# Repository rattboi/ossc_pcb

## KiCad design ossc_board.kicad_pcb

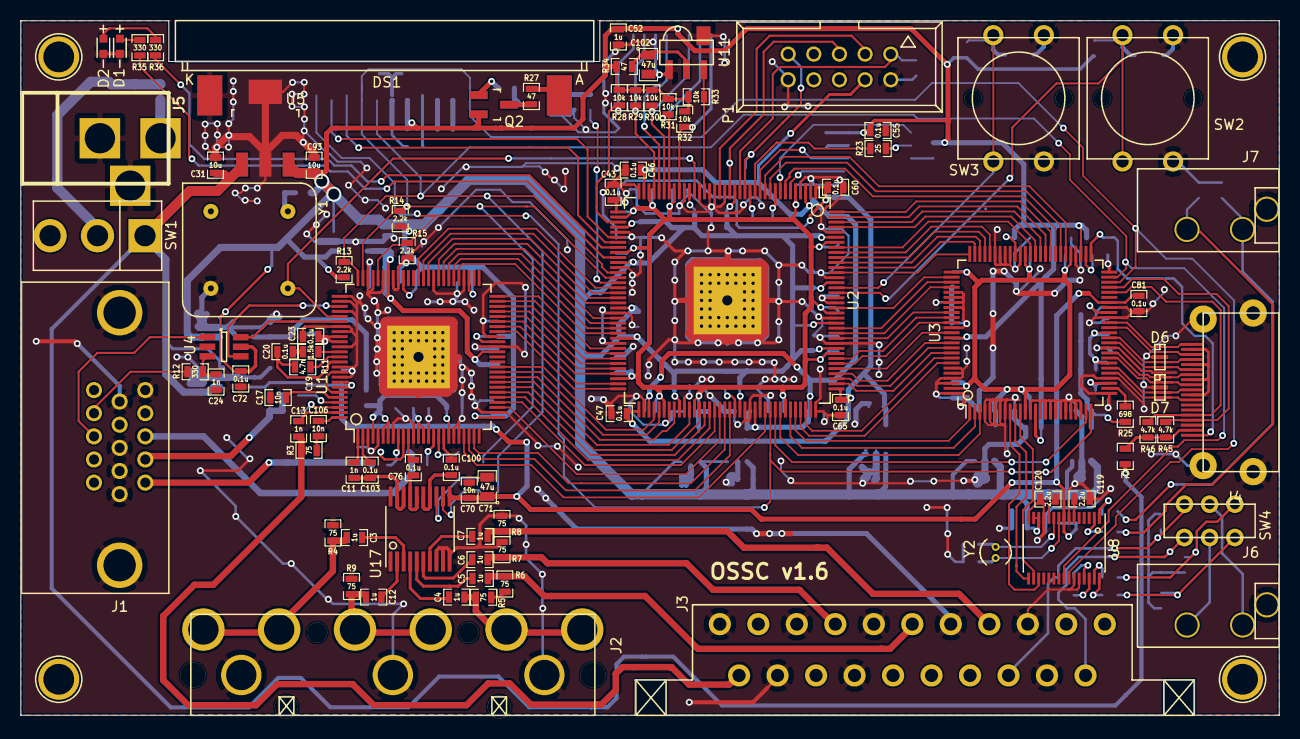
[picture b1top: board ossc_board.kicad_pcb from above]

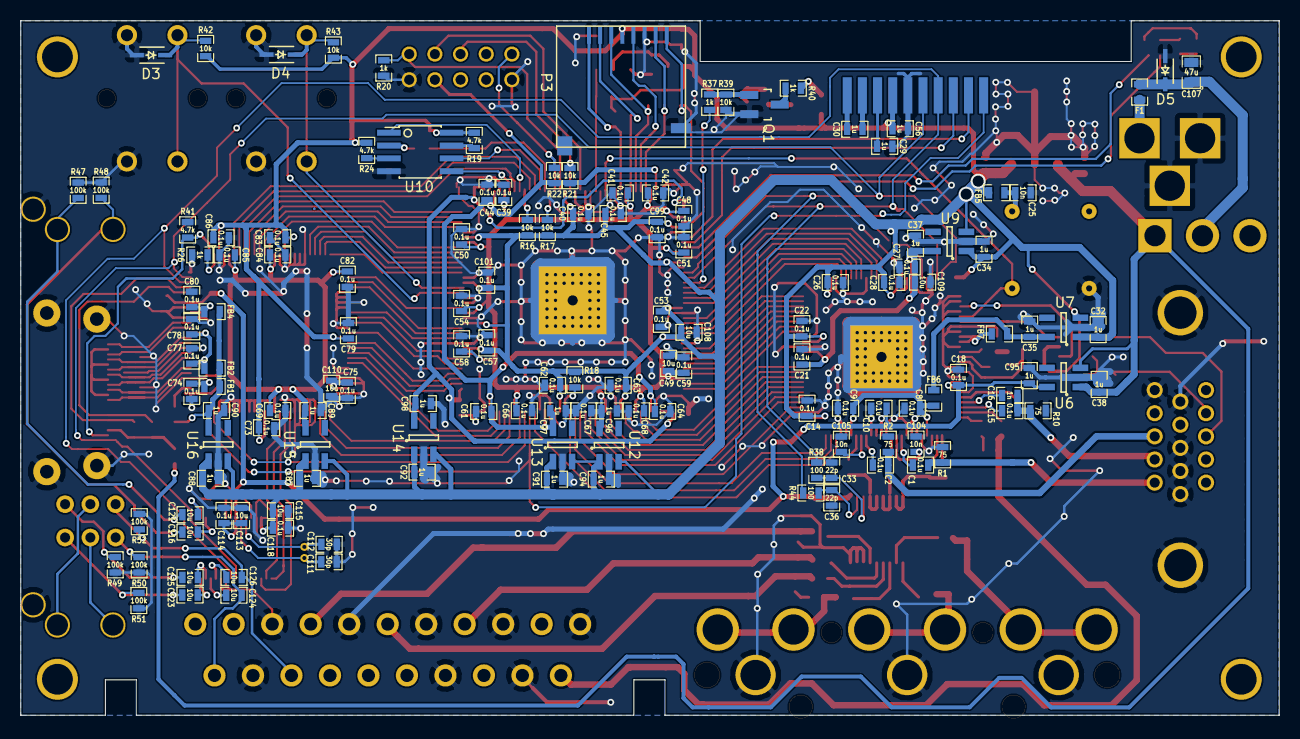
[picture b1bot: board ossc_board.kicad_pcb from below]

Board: 2 copper layers, 124.6 x 68.7 mm, 230 parts (138 on the bottom side), 197 nets.

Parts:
C1, C2, C8, C9, C10, C14, C15, C18, C20, C21, C22, C23, C26, C27, C28, C39, C40, C41, C42, C43, C44, C45, C46, C47, C48, C50, C51, C53, C54, C55, C57, C58, C59, C60, C61, C62, C63, C64, C65, C66, C67, C68, C69, C72, C73, C74, C75, C76, C77, C78, C79, C80, C81, C82, C83, C84, C85, C86, C99, C100, C101, C103, C114, C118: 0.1u; SM0603_Capa_libcms
C3, C4, C5, C6, C7, C12, C29, C30, C32, C34, C35, C37, C38, C52, C56, C87, C88, C89, C90, C91, C92, C94, C95, C96, C97, C98: 1u; SM0603_Capa_libcms
C11, C13, C16, C24: 1n; SM0603_Capa_libcms
C17, C25, C70, C104, C105, C106: 10n; SM0603_Capa_libcms
C19: 4.7n; SM0603_Capa_libcms
C31, C49, C93, C108, C109, C110, C113, C115, C116, C121, C123, C124, C125, C126: 10u; SM0603_Capa_libcms
C33, C36: 22p; SM0603_Capa_libcms
C71, C102, C107: 47u; SM0805_libcms
C111, C112: 30p; SM0603_Capa_libcms
C119, C120: 2.2u; SM0603_Capa_libcms
D1: LEDR; LED-0603
D2: LEDG; LED-0603
D3, D4, D5: SD05-7; SOD-323_Handsoldering
D6, D7: RClamp0524P; SLP2510P8
DS1: CONN_01X12; NHD-C0216CZ_vertmount
F1: F0603E1R50FSTR; SM0603_Resistor_libcms
F2: MF-FSMF020X-2; SM0603_Resistor_libcms
FB1, FB2, FB4, FB5, FB6, FB7: MPZ1608S221A; SM0603_Resistor_libcms
J1: VGA; VGA_CONN
J2: 3XRCA_CONN; 3xRCA_CONN
J3: SCART-F; SCART_CONN
J4: HDMI_CONN; HDMI_CONN-10029449-111RLF
J5: 5VDC_IN; BARREL_JACK_roundconn
J6, J7: SJ1-3533NG
MH1, MH2, MH3, MH4: CONN_1; 1pin
P1: JTAG_CONN; VASCH5x2
P3: mSD_CONN; DM3D-SF
Q1: BC847; SOT-23_Handsoldering
Q2: BC857; SOT-23_Handsoldering
R1, R2, R3, R4, R5, R6, R7, R8, R9, R10: 75; SM0603_Resistor_libcms
R11: 1.5k; SM0603_Resistor_libcms
R12, R35, R36: 330; SM0603_Resistor_libcms
R13, R14, R15: 2.2k; SM0603_Resistor_libcms
R16, R17, R18, R21, R22, R28, R29, R30, R31, R32, R33, R39, R42, R43: 10k; SM0603_Resistor_libcms
R19, R24, R41, R45, R46: 4.7k; SM0603_Resistor_libcms
R20, R26, R37, R40: 1k; SM0603_Resistor_libcms
R23: 25; SM0603_Resistor_libcms
R25: 698; SM0603_Resistor_libcms
R27, R34: 47; SM0603_Resistor_libcms
R38, R44: 100; SM0603_Resistor_libcms
R47, R48, R49, R50, R51, R52: 100k; SM0603_Resistor_libcms
SW1: SPST; SW_SPDT
SW2, SW3: SW_PUSH; SW_PUSH-SKHCBFA010
SW4: DPDT; MS22
U1: TVP7002PZP; TQFP-100_thermal
U2: EP4CE15E22; TQFP-144_thermal
U3: IT6613; TQFP-100_custom
U4: SN74LVC2G17; SOT-23-6_Handsoldering
U5: AP7361C; SOT-223_Handsoldering
U6: TLV70033; SOT-23-5_Handsoldering
U7: NCP703SN19T1G; SOT-23-5_Handsoldering
U8: PCM1862; TSSOP-30_4.4x7.8mm_Pitch0.5mm_Handsoldering
U9: TLV70019; SOT-23-5_Handsoldering
U10: S25FL216K; SOIC-8_3.9x4.9mm_Pitch1.27mm_Handsoldering
U11: IRM-V538/TR1; IRM-V5XX_TR1
U12, U14: TLV70012; SOT-23-5_Handsoldering
U13: TLV70025; SOT-23-5_Handsoldering
U15, U16: TLV70018; SOT-23-5_Handsoldering
U17: THS7353; TSSOP-20_4.4x6.5mm_Pitch0.65mm_Handsoldering
Y1: ACHL-27MHZ-EK; ACHL-OSC
Y2: 24.576MHz; ECS-3X9X

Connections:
/fpga1/ASDO: U2.6, U10.5
/fpga1/BTN0: D3.1, R42.1, SW2.1, U2.128
/fpga1/BTN1: D4.1, R43.1, SW3.1, U2.129
/fpga1/CLK27: U1.80, U2.25, Y1.5
/fpga1/DATA0: R23.1, U2.13
/fpga1/DCLK: U2.12, U10.6
/fpga1/HDMITX_HSYNC: U2.103, U3.2
/fpga1/HDMITX_INT_N: U2.100, U3.24
/fpga1/HDMITX_PCLK: U2.113, U3.88
/fpga1/HDMITX_R0: U2.137, U3.63
/fpga1/HDMITX_R1: U2.141, U3.62
/fpga1/HDMITX_R2: U2.142, U3.61
/fpga1/HDMITX_R3: U2.143, U3.60
/fpga1/HDMITX_R4: U2.144, U3.59
/fpga1/HDMITX_R5: U2.7, U3.58
/fpga1/HDMITX_R6: U2.10, U3.57
/fpga1/HDMITX_R7: U2.11, U3.56
/fpga1/HDMITX_VSYNC: U2.101, U3.3
/fpga1/IR_RX: R33.2, U2.23, U11.1
/fpga1/LCD_BLEN: R37.2, U2.51
/fpga1/LCD_CS_N: DS1.3, U2.43
/fpga1/LCD_RS: DS1.2, U2.42
/fpga1/LED0: R35.2, U2.46
/fpga1/LED1: R36.2, U2.44
/fpga1/RESET_N: DS1.1, R15.1, U1.71, U2.99, U3.25
/fpga1/SCL: DS1.4, R14.2, R38.2, U1.74, U2.50, U3.48, U8.24
/fpga1/SDA: DS1.5, R13.1, R44.1, U1.75, U2.49, U3.49, U8.23
/fpga1/SD_CLK: P3.5, U2.32
/fpga1/SD_CMD: P3.3, R30.1, U2.31
/fpga1/SD_DAT0: P3.7, R29.1, U2.33
/fpga1/SD_DAT1: P3.8, R28.1, U2.39
/fpga1/SD_DAT2: P3.1, R32.1, U2.28
/fpga1/SD_DAT3: P3.2, R31.1, U2.30
/fpga1/TCK: P1.1, R20.2, U2.16
/fpga1/TDI: P1.9, R22.2, U2.15
/fpga1/TDO: P1.3, U2.20
/fpga1/TMS: P1.5, R21.2, U2.18
/fpga1/VCCA: C44.1, C46.1, C61.1, C64.1, C97.1, P1.4, R21.1, R22.1, U2.3, U2.35, U2.75, U2.96, U2.107, U13.5
/fpga1/VCCD_PLL: C43.1, C47.1, C60.1, C65.1, C98.1, U2.1, U2.37, U2.73, U2.109, U14.5
/fpga1/VCCINT: C39.1, C41.1, C42.1, C48.1, C49.1, C50.1, C51.1, C54.1, C58.1, C59.1, C66.1, C67.1, C68.1, C96.1, U2.5, U2.29, U2.34, U2.38, U2.45, U2.70, U2.78, U2.84, U2.102, U2.116, U2.124, U2.138, U12.5
/fpga1/nCSO: U2.8, U10.1
/hdmitx1/5V: C31.1, C38.1, F2.1, SW1.1, U5.1, U6.1, U6.3
/hdmitx1/5V_FUSED: F2.2, J4.18, R45.1, R46.1
/hdmitx1/AV1_AUD_L: C126.2, J3.6, R52.1, SW4.3
/hdmitx1/AV1_AUD_R: C124.2, J3.2, R50.2, SW4.6
/hdmitx1/AV2_AUD_L: C125.2, R49.1, SW4.1
/hdmitx1/AV2_AUD_R: C123.2, R51.2, SW4.4
/hdmitx1/AV3_AUD_L: C121.1, J7.2, R47.2
/hdmitx1/AV3_AUD_R: C116.1, J7.3, R48.2
/hdmitx1/AVCC1V8: C90.1, FB1.1, FB2.1, FB4.1, R25.2, U16.5
/hdmitx1/AVDD3V3: C10.1, C18.2, C70.1, C71.1, C81.1, C95.1, C113.1, C114.1, U1.13, U1.14, U1.93, U1.94, U3.44, U6.5, U8.8, U17.11
/hdmitx1/B0: U2.105, U3.94
/hdmitx1/B1: U2.106, U3.93
/hdmitx1/B2: U2.110, U3.92
/hdmitx1/B3: U2.111, U3.91
/hdmitx1/B4: U2.112, U3.90
/hdmitx1/B5: U2.114, U3.86
/hdmitx1/B6: U2.115, U3.85
/hdmitx1/B7: U2.119, U3.84
/hdmitx1/DDC_SCL: J4.15, R46.2, U3.46
/hdmitx1/DDC_SDA: J4.16, R45.2, U3.47
/hdmitx1/DE: U2.104, U3.1
/hdmitx1/DVDD1V8: C69.1, C75.1, C82.1, C84.1, C85.1, C89.1, C110.1, U3.12, U3.55, U3.64, U3.76, U3.99, U15.5
/hdmitx1/DVDD3V3: C14.1, C22.1, C26.1, C28.1, C32.2, C34.1, C40.1, C45.1, C52.1, C53.1, C55.2, C56.2, C57.1, C62.1, C63.1, C72.1, C73.1, C79.1, C83.1, C86.1, C87.1, C88.1, C91.1, C92.1, C93.1, C94.1, C99.1, C101.1, C108.1, C115.1, C118.1, DS1.7, FB5.2, P3.4, Q2.2, R13.2, R14.1, R16.1, R17.2, R18.1, R19.2, R24.2, R28.2, R29.2, R30.2, R31.2, R32.2, R33.1, R34.2, R42.2, R43.2, U1.26, U1.41, U1.53, U1.66, U2.17, U2.26, U2.40, U2.47, U2.56, U2.62, U2.81, U2.93, U2.117, U2.122, U2.130, U2.139, U3.14, U3.53, U3.66, U3.89, U4.5, U5.3, U7.1, U7.3, U8.13, U8.14, U9.1, U9.3, U10.8, U12.1, U12.3, U13.1, U13.3, U14.1, U14.3, U15.1, U15.3, U16.1, U16.3
/hdmitx1/G0: U2.120, U3.79
/hdmitx1/G1: U2.121, U3.78
/hdmitx1/G2: U2.125, U3.77
/hdmitx1/G3: U2.132, U3.75
/hdmitx1/G4: U2.133, U3.74
/hdmitx1/G5: U2.134, U3.73
/hdmitx1/G6: U2.135, U3.72
/hdmitx1/G7: U2.136, U3.71
/hdmitx1/HPD: J4.19, R41.1, U3.51
/hdmitx1/I2S_BCK: U3.11, U8.17
/hdmitx1/I2S_DATA: U3.9, U8.18
/hdmitx1/I2S_WS: U3.10, U8.16
/hdmitx1/TMDS_CLK+: D7.4, D7.7, J4.10, U3.31
/hdmitx1/TMDS_CLK-: D7.5, D7.6, J4.12, U3.30
/hdmitx1/TMDS_D0+: D7.1, D7.10, J4.7, U3.34
/hdmitx1/TMDS_D0-: D7.2, D7.9, J4.9, U3.33
/hdmitx1/TMDS_D1+: D6.4, D6.7, J4.4, U3.37
/hdmitx1/TMDS_D1-: D6.5, D6.6, J4.6, U3.36
/hdmitx1/TMDS_D2+: D6.1, D6.10, J4.1, U3.40
/hdmitx1/TMDS_D2-: D6.2, D6.9, J4.3, U3.39
/tvp_board1/AVDD: C35.1, FB6.1, FB7.1, U7.5
/tvp_board1/AVDD_F: C8.1, C9.1, FB6.2, U1.4, U1.6, U1.7, U1.19
/tvp_board1/B0: U1.36, U2.76
/tvp_board1/B1: U1.35, U2.77
/tvp_board1/B2: U1.34, U2.80
/tvp_board1/B3: U1.33, U2.83
/tvp_board1/B4: U1.32, U2.85
/tvp_board1/B5: U1.31, U2.86
/tvp_board1/B6: U1.30, U2.87
/tvp_board1/B7: U1.29, U2.88
/tvp_board1/DVDD: C21.1, C27.1, C37.1, C109.1, U1.39, U1.69, U9.5
/tvp_board1/FID: U1.22, U2.98
/tvp_board1/G0: U1.50, U2.64
/tvp_board1/G1: U1.49, U2.65
/tvp_board1/G2: U1.48, U2.66
/tvp_board1/G3: U1.47, U2.67
/tvp_board1/G4: U1.46, U2.68
/tvp_board1/G5: U1.45, U2.69
/tvp_board1/G6: U1.44, U2.71
/tvp_board1/G7: U1.43, U2.72
/tvp_board1/HSYNC: U1.24, U2.90
/tvp_board1/PCLK: U1.28, U2.89
/tvp_board1/R0: U1.63, U2.52
/tvp_board1/R1: U1.62, U2.53
/tvp_board1/R2: U1.61, U2.54
/tvp_board1/R3: U1.59, U2.55
/tvp_board1/R4: U1.58, U2.58
/tvp_board1/R5: U1.57, U2.59
/tvp_board1/R6: U1.56, U2.60
/tvp_board1/R7: U1.55, U2.61
/tvp_board1/RGB1_B: C7.1, J3.7, R8.1
/tvp_board1/RGB1_G: C5.1, J3.11, R6.1
/tvp_board1/RGB1_R: C6.1, J3.15, R7.1
/tvp_board1/RGB1_S: C13.1, J3.20, R3.1
/tvp_board1/RGB2_B: C4.1, J2.2, R5.1
/tvp_board1/RGB2_G: C12.1, J2.1, R9.1
/tvp_board1/RGB2_R: C3.1, J2.3, R4.1
/tvp_board1/RGB3_B: C2.1, J1.3, R2.1
/tvp_board1/RGB3_G: C15.1, C16.1, J1.2, R10.2
/tvp_board1/RGB3_HS: J1.13, U4.1
/tvp_board1/RGB3_HS_B: U1.81, U4.6
/tvp_board1/RGB3_R: C1.1, J1.1, R1.1
/tvp_board1/RGB3_VS: J1.14, R12.2
/tvp_board1/RGB3_VS_B: U1.78, U4.4
/tvp_board1/RGB_12_B: C100.1, U17.14, U17.15
/tvp_board1/RGB_12_G: C11.1, C103.1, U17.18, U17.19
/tvp_board1/RGB_12_R: C76.1, U17.16, U17.17
/tvp_board1/VSYNC: U1.23, U2.91
GND: C8.2, C9.2, C10.2, C14.2, C17.1, C18.1, C21.2, C22.2, C23.2, C24.2, C25.2, C26.2, C27.2, C28.2, C29.1, C31.2, C32.1, C33.1, C34.2, C35.2, C36.2, C37.2, C38.2, C39.2, C40.2, C41.2, C42.2, C43.2, C44.2, C45.2, C46.2, C47.2, C48.2, C49.2, C50.2, C51.2, C52.2, C53.2, C54.2, C55.1, C56.1, C57.2, C58.2, C59.2, C60.2, C61.2, C62.2, C63.2, C64.2, C65.2, C66.2, C67.2, C68.2, C69.2, C70.2, C71.2, C72.2, C73.2, C74.2, C75.2, C77.2, C78.2, C79.2, C80.2, C81.2, C82.2, C83.2, C84.2, C85.2, C86.2, C87.2, C88.2, C89.2, C90.2, C91.2, C92.2, C93.2, C94.2, C95.2, C96.2, C97.2, C98.2, C99.2, C101.2, C102.2, C104.1, C105.1, C106.2, C107.2, C108.2, C109.2, C110.2, C111.2, C112.2, C113.2, C114.2, C115.2, C118.2, C119.2, C120.2, D1.2, D2.2, D3.2, D4.2, D5.2, D6.3, D6.8, D7.3, D7.8, DS1.6, DS1.12, J1.5, J1.6, J1.7, J1.8, J1.10, J2.4, J3.4, J3.5, J3.9, J3.13, J3.14, J3.17, J3.18, J3.21, J4.2, J4.5, J4.8, J4.11, J4.17, J5.2, J5.3, J6.1, J7.1, P1.2, P1.10, P3.6, Q1.2, R1.2, R2.2, R3.2, R4.2, R5.2, R6.2, R7.2, R8.2, R9.2, R10.1, R15.2, R20.1, R26.2, R39.2, R41.2, R47.1, R48.1, R49.2, R50.1, R51.1, R52.2, SW2.2, SW3.2, U1.3, U1.5, U1.8, U1.12, U1.15, U1.20, U1.21, U1.27, U1.40, U1.42, U1.54, U1.60, U1.67, U1.68, U1.70, U1.72, U1.73, U1.76, U1.77, U1.79, U1.82, U1.83, U1.86, U1.90, U1.91, U1.92, U1.95, U2.2, U2.4, U2.19, U2.21, U2.22, U2.24, U2.27, U2.36, U2.41, U2.48, U2.57, U2.63, U2.74, U2.79, U2.82, U2.94, U2.95, U2.97, U2.108, U2.118, U2.123, U2.126, U2.127, U2.131, U2.140, U3.4, U3.5, U3.6, U3.7, U3.8, U3.13, U3.15, U3.16, U3.17, U3.18, U3.19, U3.20, U3.21, U3.22, U3.23, U3.26, U3.29, U3.35, U3.41, U3.43, U3.50, U3.54, U3.65, U3.67, U3.68, U3.69, U3.70, U3.80, U3.81, U3.82, U3.83, U3.87, U3.95, U3.96, U3.97, U3.98, U3.100, U4.2, U5.2, U6.2, U7.2, U8.7, U8.12, U8.15, U8.25, U8.26, U9.2, U10.4, U11.3, U12.2, U13.2, U14.2, U15.2, U16.2, U17.8, U17.9, U17.10, Y1.4
unnamed: C1.2, U1.9
unnamed: C2.2, U1.16
unnamed: C3.2, U17.3
unnamed: C4.2, U17.4
unnamed: C5.2, U17.5
unnamed: C6.2, U17.6
unnamed: C7.2, U17.7
unnamed: C11.2, U1.1
unnamed: C12.2, U17.2
unnamed: C13.2, U1.99
unnamed: C15.2, U1.98
unnamed: C16.2, U1.97
unnamed: C17.2, U1.96
unnamed: C19.1, U1.88
unnamed: C19.2, C20.1, U1.89
unnamed: C20.2, R11.1
unnamed: C23.1, FB7.2, U1.84, U1.85
unnamed: C24.1, R12.1, U4.3
unnamed: C25.1, FB5.1, Y1.8
unnamed: C29.2, DS1.8
unnamed: C30.1, DS1.10
unnamed: C30.2, DS1.9
unnamed: C33.2, R38.1, U17.13
unnamed: C36.1, R44.2, U17.12
unnamed: C74.1, FB1.2, U3.28
unnamed: C76.2, U1.11
unnamed: C77.1, C78.1, FB2.2, U3.32, U3.38
unnamed: C80.1, FB4.2, U3.42
unnamed: C100.2, U1.18
unnamed: C102.1, R34.1, U11.2
unnamed: C103.2, U1.2
unnamed: C104.2, U1.10
unnamed: C105.2, U1.17
unnamed: C106.1, U1.100
unnamed: C107.1, D5.1, F1.2, SW1.2
unnamed: C111.1, U8.9, Y2.1
unnamed: C112.1, U8.10, Y2.2
unnamed: C116.2, U8.2
unnamed: C119.1, U8.6
unnamed: C120.1, U8.11
unnamed: C121.2, U8.1
unnamed: C123.1, U8.30
unnamed: C124.1, U8.28
unnamed: C125.1, U8.29
unnamed: C126.1, U8.27
unnamed: D1.1, R35.1
unnamed: D2.1, R36.1
unnamed: DS1.11, R27.1
unnamed: F1.1, J5.1
unnamed: J6.2, SW4.2
unnamed: J6.3, SW4.5
unnamed: Q1.1, R37.1, R39.1
unnamed: Q1.3, R40.1
unnamed: Q2.1, R40.2
unnamed: Q2.3, R27.2
unnamed: R11.2, U1.87
unnamed: R16.2, U2.9
unnamed: R17.1, U2.14
unnamed: R18.2, U2.92
unnamed: R19.1, U10.7
unnamed: R23.2, U10.2
unnamed: R24.1, U10.3
unnamed: R25.1, U3.27
unnamed: R26.1, U3.52

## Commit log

2017-05-17 Replaced oval drilled slots, as OSHPark doesn't support them
2017-05-31 Changed footprint of headphone jack to circular drill
    Also, verified DRC rules pass for OSHPark
